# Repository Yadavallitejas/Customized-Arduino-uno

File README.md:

### **Custom Arduino Uno Documentation Using ATmega328P**

This documentation provides a detailed description of designing a custom Arduino Uno using the ATmega328P microcontroller. The project also incorporates the following components:
- **7-segment display (SSD)**
- **CD4511BE** as the SSD driver IC
- **L293D** for motor driving
- **Programmable debugging capability**
- **Potentiometer**
- **RGB LED with switch**
- **Power supply using 7805 voltage regulator**
- **16 MHz external oscillator** for the microcontroller.

---

## **1. Block Diagram**

The main components of the custom Arduino are interconnected as follows:

```
+---------------------------+
|                           |
|    ATmega328P             |
|    (Microcontroller)      |
|                           |
|  +---------------------+  |
|  | 7-Segment Display    |  |
|  |   CD4511BE Driver    |  |
|  +---------------------+  |
|                           |
|  +---------------------+  |
|  | Motor Driver         |  |
|  |   L293D              |  |
|  +---------------------+  |
|                           |
|  +---------------------+  |
|  | RGB LED and Switch   |  |
|  +---------------------+  |
|                           |
|  +---------------------+  |
|  | Potentiometer        |  |
|  +---------------------+  |
|                           |
|  +---------------------+  |
|  | Power Supply (7805)  |  |
|  +---------------------+  |
|                           |
+---------------------------+
```

## **2. Hardware Components**

### **2.1 ATmega328P Microcontroller**

- **Core component**: ATmega328P is the microcontroller used in the original Arduino Uno.
- **Pinout**: 28 pins in total.
- **Clock Speed**: 16 MHz external crystal oscillator (necessary for stable and precise timing).
- **Programming**: The microcontroller can be programmed via a serial interface (FTDI or USB to UART converter).
- **Reset circuit**: A 10k pull-up resistor on the reset pin with a capacitor connected to ground ensures proper reset behavior.

### **2.2 7-Segment Display with CD4511BE IC**

- **Display Type**: Common Cathode 7-segment display.
- **Driver IC (CD4511BE)**: The CD4511BE is a BCD to 7-segment driver IC. It converts the binary coded decimal input from the ATmega328P to a corresponding output to control the SSD.
  - **Connections**:
    - Input pins: The ATmega328P sends a 4-bit BCD code to CD4511BE on four input pins.
    - Output pins: These connect to the SSD to control the segments (a-g).

### **2.3 Motor Driver with L293D**

- **Motor Control**: L293D is a dual H-bridge motor driver IC used to control DC motors or stepper motors.
- **Pinout**: L293D has 16 pins.
  - **Enable pins**: Control the motor's operation by enabling or disabling the H-bridges.
  - **Input pins**: Controlled by the ATmega328P to set the motor direction and speed.
  - **Output pins**: Connect to the motor to provide power for motor rotation.

### **2.4 Potentiometer**

- **Function**: Used to adjust input values, typically for adjusting motor speed or LED brightness.
- **Connection**: Connect the potentiometer to one of the analog input pins (A0-A5) of the ATmega328P.
- **Operation**: The varying resistance changes the voltage, which is read by the ATmega328P as an analog input signal.

### **2.5 RGB LED with Switch**

- **RGB LED**: A tri-color LED that can be controlled to display a range of colors.
- **Connections**: The Red, Green, and Blue pins of the LED connect to three digital pins on the ATmega328P, each with a current-limiting resistor (typically 220Ω).
- **Switch**: A push-button switch can be connected to a digital pin to toggle the LED on or off.

### **2.6 Power Supply with 7805 Voltage Regulator**

- **7805 IC**: A voltage regulator that outputs a stable 5V from a higher input voltage (e.g., 9V or 12V).
- **Capacitors**: Typically, a 0.1 µF capacitor is placed between the input pin and ground, and a 0.1 µF capacitor between the output pin and ground for filtering.
- **Power supply**: Provides 5V to the ATmega328P and other components.

### **2.7 16 MHz External Oscillator**

- **Crystal Oscillator**: The ATmega328P requires a 16 MHz external crystal oscillator to operate at the standard Arduino clock frequency.
- **Capacitors**: Two 22 pF capacitors are connected to the crystal to stabilize the oscillations.

### **2.8 Programmable Debugging (Prog Debug)**

- **ISP Header**: Include a 6-pin in-system programming (ISP) header to program and debug the ATmega328P using an external programmer.
  - **Pins**: MISO, MOSI, SCK, RESET, VCC, GND.
- **UART Interface**: Connect pins (TX, RX) to a USB-to-serial converter for debugging and loading code via the Arduino IDE.

---

## **3. Circuit Schematic and Wiring**

Here’s how each component is connected to the ATmega328P.

### **3.1 ATmega328P Connections**
- **Power Supply**: The 7805 IC regulates the input voltage to 5V, which is supplied to the VCC and AVCC pins.
- **Ground Pins**: GND of the power supply is connected to the GND pins of the ATmega328P.
- **Reset Pin**: Connect a 10kΩ resistor between the reset pin and VCC. Also, add a 0.1µF capacitor between the reset pin and ground.
- **16 MHz Oscillator**: Connect the crystal between XTAL1 and XTAL2 pins. Place two 22 pF capacitors between these pins and ground.
- **LED**: Connect a 220Ω resistor in series with the LED to digital pin 13.

### **3.2 7-Segment Display with CD4511BE**
- **BCD Inputs** (A-D): Connect four digital pins from the ATmega328P to the CD4511BE’s A, B, C, and D inputs.
- **7-segment Outputs**: Connect the output pins of the CD4511BE (a, b, c, d, e, f, g) to the respective segments of the SSD.
- **Common Cathode**: Connect the common cathode of the SSD to ground.

### **3.3 Motor Driver with L293D**
- **Motor Inputs**: Connect the motor control pins (IN1, IN2, IN3, IN4) of L293D to four digital output pins of the ATmega328P.
- **Motor Power**: Connect the motor’s power supply to the L293D's VCC and ground.
- **Enable Pins**: Connect the enable pins of the L293D to 5V to activate the H-bridge.

### **3.4 Potentiometer**
- **Wiper Pin**: Connect the wiper pin of the potentiometer to one of the analog pins (e.g., A0).
- **Other Pins**: Connect one pin to 5V and the other to GND.

### **3.5 RGB LED and Switch**
- **RGB LED**: Connect the RGB LED's cathode to ground, and the red, green, and blue pins to three PWM-enabled digital pins (e.g., D9, D10, D11) via 220Ω resistors.
- **Switch**: Connect the switch between a digital pin (e.g., D2) and ground, with a 10kΩ pull-up resistor between the pin and VCC.

### **3.6 Power Supply (7805)**
- **Input Voltage**: Connect a 9V or 12V power source to the input of the 7805.
- **Output**: Connect the output of the 7805 to the VCC of the ATmega328P.

---

## **4. Software Implementation**
- by using avrdude software install microcontroller code which is present in arduino ide software which is specified to atmega328p
1. **Arduino IDE Setup**:
   - Install the **ATmega328P** board in the Arduino IDE.
   - Select the correct **board** and **port** in the IDE.

2. **7-Segment Display Control**:
   - Use the digitalWrite() function to send a BCD code to the CD4511BE to display the corresponding number.

3. **Motor Control**:
   - Use digitalWrite() and analogWrite() to control the L293D and regulate motor speed and direction.

4. **RGB LED**:
   - Use analogWrite() on the RGB pins to mix colors by varying PWM duty cycles.

5. **Potentiometer Input**:
   - Read the analog input from the potentiometer using analogRead() and map the value to motor speed or LED brightness.

6. **Switch Control**:
   - Use digitalRead() to detect the switch state and toggle the RGB LED.

---

## **5. Conclusion**

This custom Arduino Uno design with the ATmega328P is tailored for various functionalities like motor control, display, sensor input, and debugging.

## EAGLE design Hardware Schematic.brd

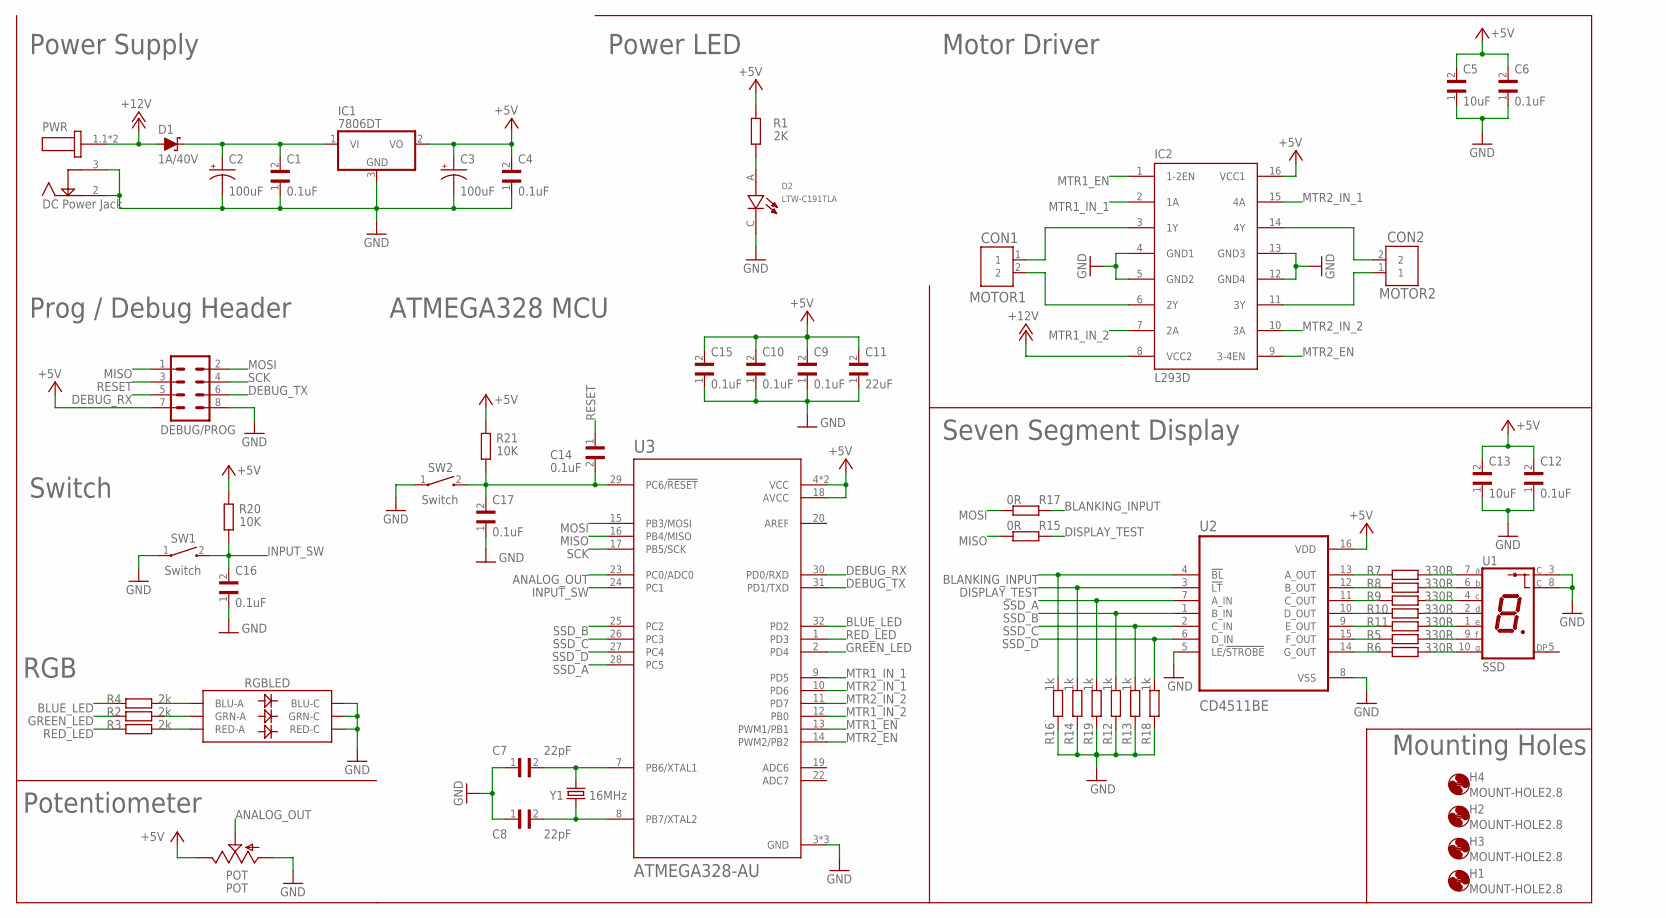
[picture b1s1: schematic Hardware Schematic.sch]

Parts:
C1, C4, C6, C9, C10, C12, C14, C15, C16, C17: 0.1uF; C0603
C2, C3: 100uF; CPOL-RADIAL-2.5MM-6.5MM
C5, C13: 10uF; C0603
C7, C8: 22pF; C0603
C11: 22uF; C0603
CON1: MOTOR1; CONN_282836-2
CON2: MOTOR2; CONN_282836-2
D1: 1A/40V; SMA-DIODE
D2: LTW-C191TLA; LEDC1608X65N
DEBUG/PROG: MA04-2
H1, H2, H3, H4: MOUNT-HOLE2.8; 2,8
IC1: 7806DT; TO252
IC2: L293D; DIL16
POT: POT; S64W
PWR: DC Power Jack; GCT_DCJ200-05-A-XX-X_REVA
R1: 2K; R0603
R2, R3, R4: 2k; R0603
R5, R6, R7, R8, R9, R10, R11: 330R; R0603
R12, R13, R14, R16, R18, R19: 1k; R0603
R15, R17: 0R; R0603
R20, R21: 10K; R0603
RGBLED: LED-RGBNO_IC; LED-TRICOLOR-5050
SW1, SW2: Switch; SW_1437566-3
U1: SSD; LED_SC52-11HWA
U2: CD4511BE; DIP794W45P254L1969H508Q16
U3: ATMEGA328-AU; QFP80P900X900X120-32N
Y1: 16MHz; HC49US

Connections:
+5V: C3.1 (+), C4.2, C5.2, C6.2, C9.2, C10.2, C11.2, C12.2, C13.2, C15.2, DEBUG/PROG.7, IC1.2 (VO), IC2.16 (VCC1), POT.E, R1.2, R20.2, R21.2, U2.16 (VDD), U3.4 (VCC), U3.6 (VCC), U3.18 (AVCC)
+12V: D1.A, IC2.8 (VCC2), PWR.1.1 (1), PWR.1.2 (1)
ANALOG_OUT: POT.S, U3.23 (PC0/ADC0)
BLANKING_INPUT: R16.2, R17.1, U2.4 (!BL)
BLUE_LED: R4.1, U3.32 (PD2)
DEBUG_RX: DEBUG/PROG.5, U3.30 (PD0/RXD)
DEBUG_TX: DEBUG/PROG.6, U3.31 (PD1/TXD)
DISPLAY_TEST: R14.2, R15.1, U2.3 (!LT)
GND: C1.1, C2.2 (-), C3.2 (-), C4.1, C5.1, C6.1, C7.1, C8.1, C9.1, C10.1, C11.1, C12.1, C13.1, C15.1, C16.1, C17.1, D2.C, DEBUG/PROG.8, IC1.3 (GND), IC2.4 (GND1), IC2.5 (GND2), IC2.12 (GND4), IC2.13 (GND3), POT.A, PWR.2, PWR.3, R12.1, R13.1, R14.1, R16.1, R18.1, R19.1, RGBLED.4 (BLU-C), RGBLED.5 (RED-C), RGBLED.6 (GRN-C), SW1.1, SW2.1, U1.3 (C), U1.8 (C), U2.5 (LE/!STROBE), U2.8 (VSS), U3.3 (GND), U3.5 (GND), U3.21 (GND)
GREEN_LED: R2.1, U3.2 (PD4)
INPUT_SW: C16.2, R20.1, SW1.2, U3.24 (PC1)
MISO: DEBUG/PROG.1, R15.2, U3.16 (PB4/MISO)
MOSI: DEBUG/PROG.2, R17.2, U3.15 (PB3/MOSI)
MTR1_EN: IC2.1 (1-2EN), U3.13 (PWM1/PB1)
MTR1_IN_1: IC2.2 (1A), U3.9 (PD5)
MTR1_IN_2: IC2.7 (2A), U3.12 (PB0)
MTR2_EN: IC2.9 (3-4EN), U3.14 (PWM2/PB2)
MTR2_IN_1: IC2.15 (4A), U3.10 (PD6)
MTR2_IN_2: IC2.10 (3A), U3.11 (PD7)
unnamed: R3.2, RGBLED.2 (RED-A)
unnamed: R2.2, RGBLED.1 (GRN-A)
unnamed: R4.2, RGBLED.3 (BLU-A)
unnamed: R7.1, U2.13 (A_OUT)
unnamed: R8.1, U2.12 (B_OUT)
unnamed: R9.1, U2.11 (C_OUT)
unnamed: R10.1, U2.10 (D_OUT)
unnamed: R11.1, U2.9 (E_OUT)
unnamed: R5.1, U2.15 (F_OUT)
unnamed: R6.1, U2.14 (G_OUT)
unnamed: R7.2, U1.7 (A)
unnamed: R8.2, U1.6 (B)
unnamed: R9.2, U1.4 (C)
unnamed: R10.2, U1.2 (D)
unnamed: R11.2, U1.1 (E)
unnamed: R5.2, U1.9 (F)
unnamed: R6.2, U1.10 (G)
unnamed: CON2.1, IC2.11 (3Y)
unnamed: D2.A, R1.1
unnamed: C1.2, C2.1 (+), D1.C, IC1.1 (VI)
unnamed: C8.2, U3.8 (PB7/XTAL2), Y1.1
unnamed: C7.2, U3.7 (PB6/XTAL1), Y1.2
unnamed: C14.2, C17.2, R21.1, SW2.2, U3.29 (PC6/!RESET)
unnamed: CON1.1, IC2.3 (1Y)
unnamed: CON1.2, IC2.6 (2Y)
unnamed: CON2.2, IC2.14 (4Y)
RED_LED: R3.1, U3.1 (PD3)
RESET: C14.1, DEBUG/PROG.3
SCK: DEBUG/PROG.4, U3.17 (PB5/SCK)
SSD_A: R19.2, U2.7 (A_IN), U3.28 (PC5)
SSD_B: R12.2, U2.1 (B_IN), U3.25 (PC2)
SSD_C: R13.2, U2.2 (C_IN), U3.26 (PC3)
SSD_D: R18.2, U2.6 (D_IN), U3.27 (PC4)

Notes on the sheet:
Power Supply
Power LED
ATMEGA328 MCU
Prog / Debug Header
Switch
RGB
Potentiometer
Motor Driver
Seven Segment Display
Mounting Holes

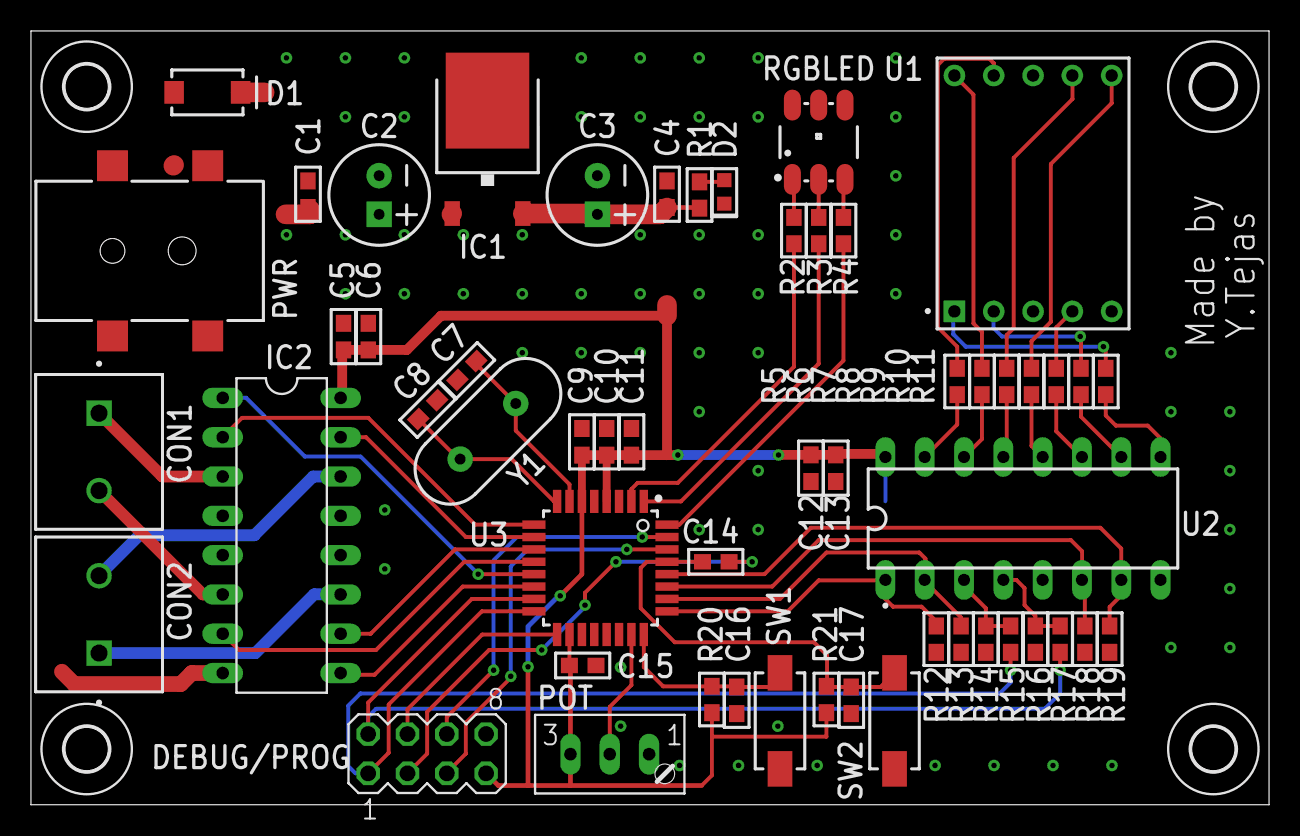
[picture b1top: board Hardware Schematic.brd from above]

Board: 2 copper layers, 80.0 x 50.0 mm, 58 parts (0 on the bottom side), 52 nets.

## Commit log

2024-10-11 Documentation README.md

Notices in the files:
parts and their libraries:
SparkFun-LED: Licensing: Creative Commons ShareAlike 4.0 International - https://creativecommons.org/licenses/by-sa/4.0
